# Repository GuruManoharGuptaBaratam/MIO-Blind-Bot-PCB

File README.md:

<div align="center">

# MIO-Blind-Bot-PCB

**Custom hardware design for MIO — a wearable assistive device for blind and low-vision users**

</div>

---

## About This Repository

This repository contains the complete PCB hardware design for **MIO**, a dual-ESP32 wearable assistive device. The board serves as the central interconnect and power-management platform of the system, tying together the compute modules, motion sensing, camera pan-tilt actuation, display feedback, and battery power delivery into a single wearable-ready design.

This is a hardware-only repository — schematics, PCB layout, manufacturing outputs, and supporting documentation live here. Firmware for the system is maintained separately.

### Key Subsystems

- **Dual ESP32 compute architecture** — separate Core and Inference module footprints
- **ESP32-CAM interconnect** — pan-tilt servo header + camera signal breakout
- **Power management** — single-cell Li-ion BMS input, with onboard 5V (CA-1235) and 3.3V (LM2596) regulation stages
- **IMU integration** — MPU6050 motion/orientation sensor interface
- **Display interface** — 1.8" ST7735 TFT (SPI) connector
- **Servo control headers** — MG90S-compatible pan/tilt outputs

---

## Board Renders

<div align="center">

| Front | Back |
|:---:|:---:|
|  |  |

**[▶ Watch the 3D board walkthrough](Documentation/MIO-3D-Video.mp4)**

</div>

---

## PCB Layout

<div align="center">

</div>

---

## Schematics

The full schematic set is available as PDF for quick review without opening KiCad:

- [MIO Schematic — Sheet 1](Documentation/MIO-Schematic%281%29.pdf)
- [MIO Schematic — Sheet 2](Documentation/MIO-Schematic%282%29.pdf)

For the editable source, see [`Hardware/MIO-Blind BOT.kicad_sch`](Hardware/MIO-Blind%20BOT.kicad_sch).

---

## Footprints & 3D Models

Custom footprints and 3D models used in this design are included so the project can be opened and rendered without missing library references. Each subfolder is a standalone KiCad footprint library (`.pretty`-style) containing the `.kicad_mod` definition and matching `.step` model.

| Folder | Used For |
|---|---|
| [`BMS-2S 20A`](Footprints/BMS-2S%2020A) | Battery management module (U8) |
| [`CA-1235 (Step-Down)`](Footprints/CA-1235%20%28Step-Down%29) | 5V step-down converter (U5) |
| [`ESP32-CAM`](Footprints/ESP32-CAM) | ESP32-CAM module footprint |
| [`ESP32-DEVKITC-32E`](Footprints/ESP32-DEVKITC-32E) | ESP32 DevKit footprint (Core / Inference modules) |
| [`LM2596-Buck(DC-DC)`](Footprints/LM2596-Buck%28DC-DC%29) | 3.3V buck converter (U12) |
| [`MIO-PCB-Logo`](Footprints/MIO-PCB-Logo) | Silkscreen logo footprint |
| [`ON-OFF Switch`](Footprints/ON-OFF%20Switch) | Power on/off switch |

**To use these in KiCad:**

1. Open **Preferences → Manage Footprint Libraries**.
2. Add each folder under [`Footprints/`](Footprints) as its own library entry (or point to the parent folder if your KiCad version supports nested library discovery).
3. Confirm each footprint's **3D Models** tab (Footprint Properties) is correctly linked to its `.step` file — this is what drives the renders in the [Board Renders](#board-renders) section above.

---

## Manufacturing Files

Ready-to-fabricate outputs are provided for direct submission to a PCB manufacturer (JLCPCB, PCBWay, or equivalent), plus a Bill of Materials for sourcing components.

<div align="center">

### [⬇ Download Gerbers (MIO-Gerber.zip)](Manfacturing/MIO-Gerber.zip) &nbsp;|&nbsp; [⬇ Download BOM (MIO-Blind BOT.csv)](Manfacturing/MIO-Blind%20BOT.csv)

</div>

| File / Folder | Description |
|---|---|
| [`MIO-Gerber.zip`](Manfacturing/MIO-Gerber.zip) | Complete Gerber file set for fabrication |
| [`MIO-Gerbers/`](Manfacturing/MIO-Gerbers) | Unpacked Gerber layer files |
| [`MIO-Drill/`](Manfacturing/MIO-Drill) | Drill files (NC drill / Excellon) |
| [`MIO-Blind BOT.csv`](Manfacturing/MIO-Blind%20BOT.csv) | Bill of Materials (BOM) |

---

## Repository Structure

```
MIO-Blind-Bot-PCB/
├── Documentation/
│   ├── MIO-3D-PCB-Back.png
│   ├── MIO-3D-PCB-Front.png
│   ├── MIO-3D-Video.mp4
│   ├── MIO-Complete-3D.png
│   ├── MIO-PCB-Layout.png
│   ├── MIO-Schematic(1).pdf
│   └── MIO-Schematic(2).pdf
├── Hardware/
│   ├── MIO-Blind BOT.kicad_pcb
│   ├── MIO-Blind BOT.kicad_pro
│   └── MIO-Blind BOT.kicad_sch
├── Manfacturing/
│   ├── MIO-Drill/
│   ├── MIO-Gerbers/
│   ├── MIO-Blind BOT.csv
│   └── MIO-Gerber.zip
├── Footprints/
│   ├── BMS-2S 20A/
│   ├── CA-1235 (Step-Down)/
│   ├── ESP32-CAM/
│   ├── ESP32-DEVKITC-32E/
│   ├── LM2596-Buck(DC-DC)/
│   ├── MIO-PCB-Logo/
│   └── ON-OFF Switch/
├── Symbols/
│   └── MIO-Logo.gif
└── README.md
```

---

## Design Environment

| | |
|---|---|
| **EDA Tool** | [KiCad](https://www.kicad.org/) 10.0 |
| **Layers** | 2-layer (F.Cu / B.Cu) |
| **Design Type** | Wearable power & interconnect board |
| **First Revision** | First custom PCB design for the MIO project |

---

## Getting Started

To open and edit this design locally:

1. Install [KiCad](https://www.kicad.org/download/) (v8 or later recommended).
2. Clone this repository:
   ```bash
        git clone https://github.com/GuruManoharGuptaBaratam/MIO-Blind-Bot-PCB.git
   ```
3. Open [`Hardware/MIO-Blind BOT.kicad_pro`](Hardware/MIO-Blind%20BOT.kicad_pro) in KiCad.

To order the board as-is, download [`MIO-Gerber.zip`](Manfacturing/MIO-Gerber.zip) above and upload it directly to your preferred PCB fabricator. Use [`MIO-Blind BOT.csv`](Manfacturing/MIO-Blind%20BOT.csv) to source and place components.

---

## Roadmap

- [x] Footprint library (`.kicad_mod`) and 3D models (`.step`)
- [ ] Bring-up and test notes

---

## License

License to be finalized — see repository for updates.

---

<div align="center">
<sub>Part of the <b>MIO</b> project.</sub>
</div>

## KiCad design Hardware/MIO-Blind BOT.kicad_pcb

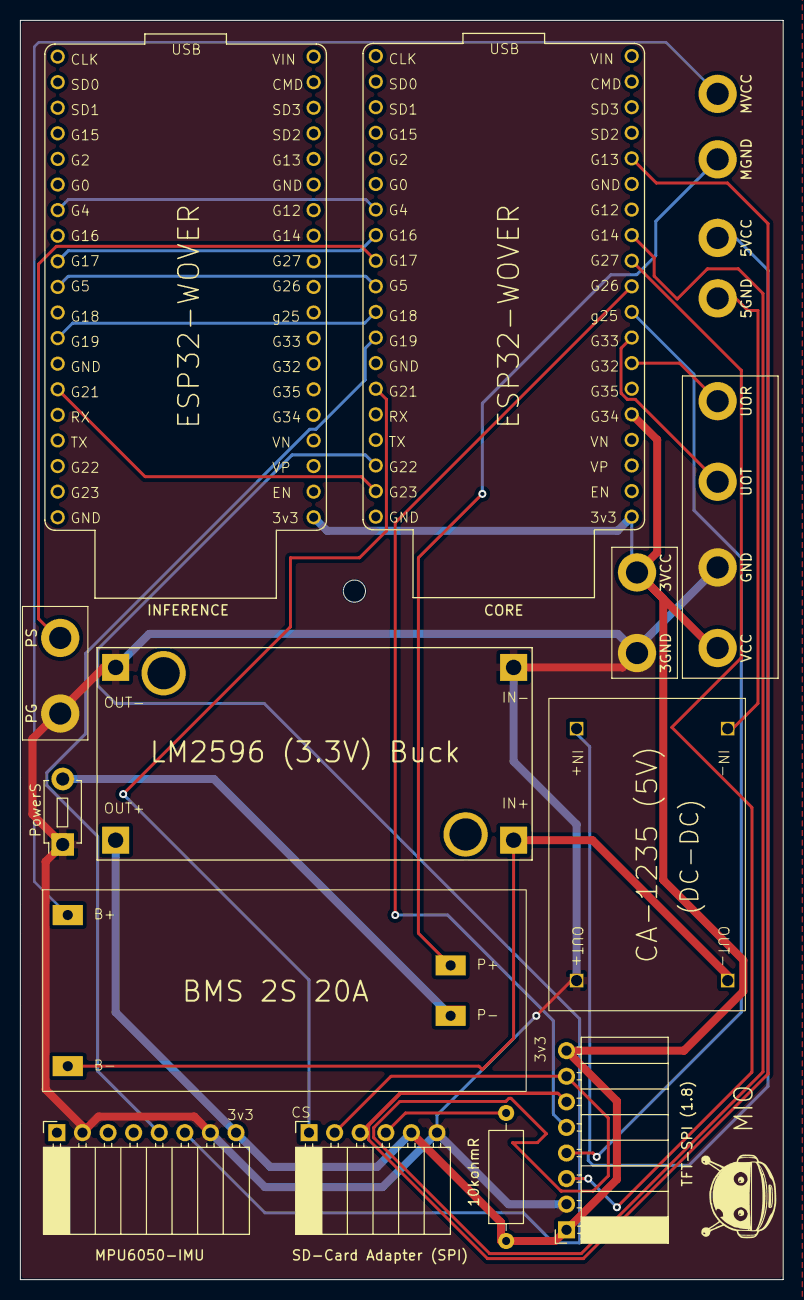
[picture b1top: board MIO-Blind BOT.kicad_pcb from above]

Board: 2 copper layers, 75.7 x 125.0 mm, 22 parts (0 on the bottom side), 25 nets.

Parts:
3GND: GND(3.3V); MountingHole_2.2mm_M2_DIN965_Pad
3VCC: VCC(3.3V); MountingHole_2.2mm_M2_DIN965_Pad
5GND: GND; MountingHole_2.2mm_M2_DIN965_Pad
5VCC: VCC; MountingHole_2.2mm_M2_DIN965_Pad
10kohmR: (10kohm); R_Axial_DIN0309_L9.0mm_D3.2mm_P12.70mm_Horizontal
BMS 2S 20A: BMS 1S-NC; BMS-2S 20A
CA-1235 (5V): CA-1235 (5V); Converter_MP1495_Module
CORE: ESP32; MODULE_ESP32-DEVKITC-32E
GND: GND; MountingHole_2.2mm_M2_DIN965_Pad
INFERENCE: ESP32; MODULE_ESP32-DEVKITC-32E
MGND: Main (GND); MountingHole_2.2mm_M2_DIN965_Pad
MPU6050-IMU: MPU6050; PinSocket_1x08_P2.54mm_Horizontal
MVCC: Main (VCC); MountingHole_2.2mm_M2_DIN965_Pad
PG: BG; MountingHole_2.2mm_M2_DIN965_Pad
PS: BI; MountingHole_2.2mm_M2_DIN965_Pad
PowerS: BUTTON; SW_PUSH_1P1T_6x3.5mm_H5.0_APEM_MJTP1250
SD-Card Adapter (SPI): SD card adapter (SPI); PinSocket_1x06_P2.54mm_Horizontal
TFT-SPI (1.8): TFT SPI (1.8); PinSocket_1x08_P2.54mm_Horizontal
U12: LM2596 (3.3v); CONV_USA_MC00100
UOR: UOR; MountingHole_2.2mm_M2_DIN965_Pad
UOT: UOT; MountingHole_2.2mm_M2_DIN965_Pad
VCC: VCC; MountingHole_2.2mm_M2_DIN965_Pad

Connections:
/+3V3_PWR: 3VCC.1 (1_1), 10kohmR.1, CORE.3V3, CORE.D34, INFERENCE.3V3, MPU6050-IMU.8 (VCC-3.3V), SD-Card Adapter (SPI).5 (VCC), TFT-SPI (1.8).1 (VCC), TFT-SPI (1.8).8 (LED), U12.4 (OUT+), VCC.1 (1_1)
/+5V_PWR: 5VCC.1 (1_1), CA-1235 (5V).2 (Out+)
/GND: 3GND.1 (1_1), CA-1235 (5V).4 (In-), GND.1 (1_1), MPU6050-IMU.2 (AD0), MPU6050-IMU.7 (GND), PG.1 (1_1), PowerS.1, SD-Card Adapter (SPI).6 (GND), TFT-SPI (1.8).2 (GND), U12.2 (IN-), U12.3 (OUT-)
/I2C_SCL: CORE.D22 (SCL/D22), MPU6050-IMU.6 (SCL)
/I2S_SDA: CORE.D19, MPU6050-IMU.5 (SDA)
/PWR_SW_IN: BMS 2S 20A.3 (P-), PowerS.2
/SD_CS: CORE.D21 (SDA/D21), SD-Card Adapter (SPI).1 (CS)
/SD_MISO: 10kohmR.2, SD-Card Adapter (SPI).4 (MISO)
/SD_MOSI: CORE.D13, SD-Card Adapter (SPI).3 (MOSI), TFT-SPI (1.8).6 (SDA)
/SD_SCK: CORE.D14, SD-Card Adapter (SPI).2 (SCK), TFT-SPI (1.8).7 (SCK)
/TFT_CS: CORE.D27, TFT-SPI (1.8).3 (CS)
/TFT_DC: CORE.D26, TFT-SPI (1.8).5 (A0)
/TFT_RST: CORE.D25, TFT-SPI (1.8).4 (RST)
/VBAT+: BMS 2S 20A.4 (B1-), MGND.1 (1_1)
/VBAT-: BMS 2S 20A.1 (B1+), MVCC.1 (1_1)
/VCC_SYS: BMS 2S 20A.2 (P+), CA-1235 (5V).3 (In+), U12.1 (IN+)
unnamed: CORE.D33, UOT.1 (1_1)
unnamed: CORE.D32, UOR.1 (1_1)
unnamed: CORE.D4, INFERENCE.D4
unnamed: CORE.D5, INFERENCE.D5
unnamed: CORE.D18, INFERENCE.D19
unnamed: CORE.D16 (RX2/D16), INFERENCE.D17 (TX2/D17)
unnamed: CORE.D17 (TX2/D17), PS.1 (1_1)
unnamed: CORE.D23, INFERENCE.D21 (SDA/D21)
unnamed: 5GND.1 (1_1), CA-1235 (5V).1 (Out-)

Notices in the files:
README.md:
License: TBD
